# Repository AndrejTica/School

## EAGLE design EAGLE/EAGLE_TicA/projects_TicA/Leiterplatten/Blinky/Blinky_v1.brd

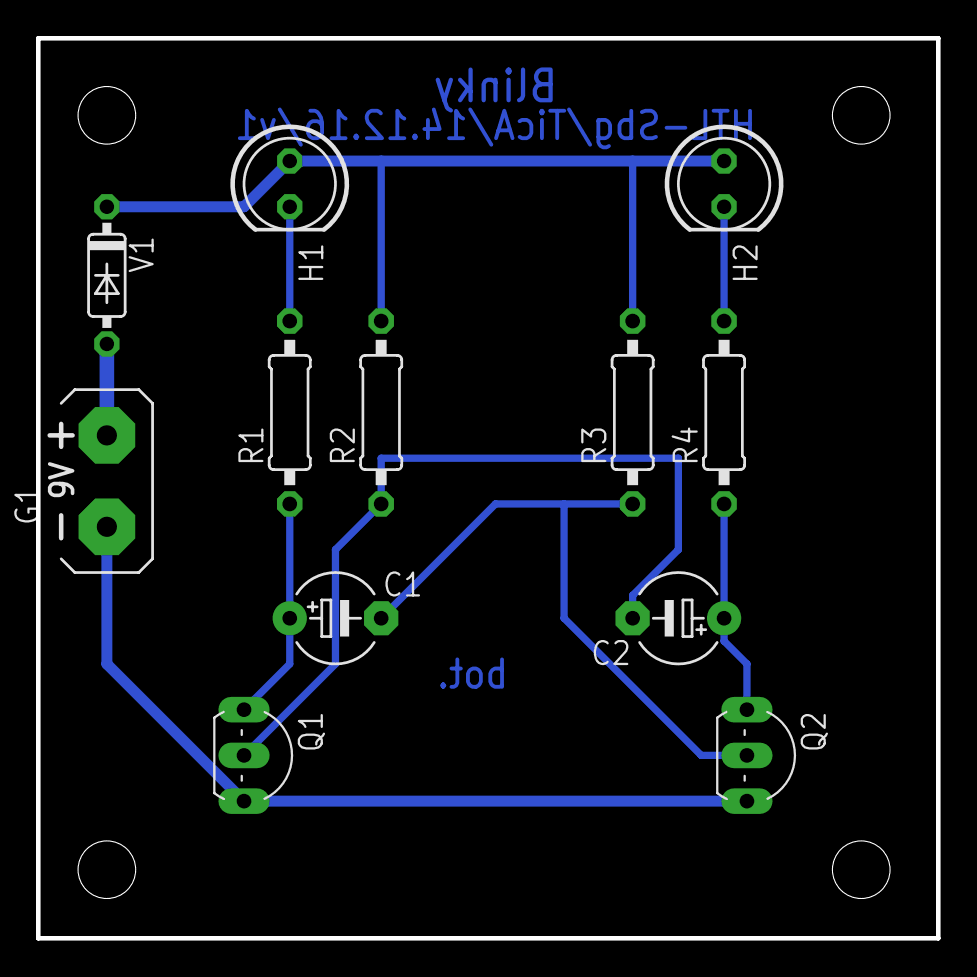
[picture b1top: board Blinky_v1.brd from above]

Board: 2 copper layers, 50.0 x 50.0 mm, 12 parts (0 on the bottom side), 9 nets.

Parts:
C1, C2: 22u; E5-5
G1: AB9V9V; AB9V
H1: Rt; LED5MM
H2: Gn; LED5MM
Q1, Q2: BC546B; TO92-EBC
R1, R4: 330R; 0207/10
R2, R3: 4k7; 0207/10
V1: 1N4148; DO35-7

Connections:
+9V: G1.+, V1.A
GND: G1.-, Q1.E, Q2.E
unnamed: H1.A, H2.A, R2.2, R3.2, V1.C
unnamed: H2.K, R4.2
unnamed: H1.K, R1.2
unnamed: C1.+, Q1.C, R1.1
unnamed: C2.-, Q1.B, R2.1
unnamed: C2.+, Q2.C, R4.1
unnamed: C1.-, Q2.B, R3.1
